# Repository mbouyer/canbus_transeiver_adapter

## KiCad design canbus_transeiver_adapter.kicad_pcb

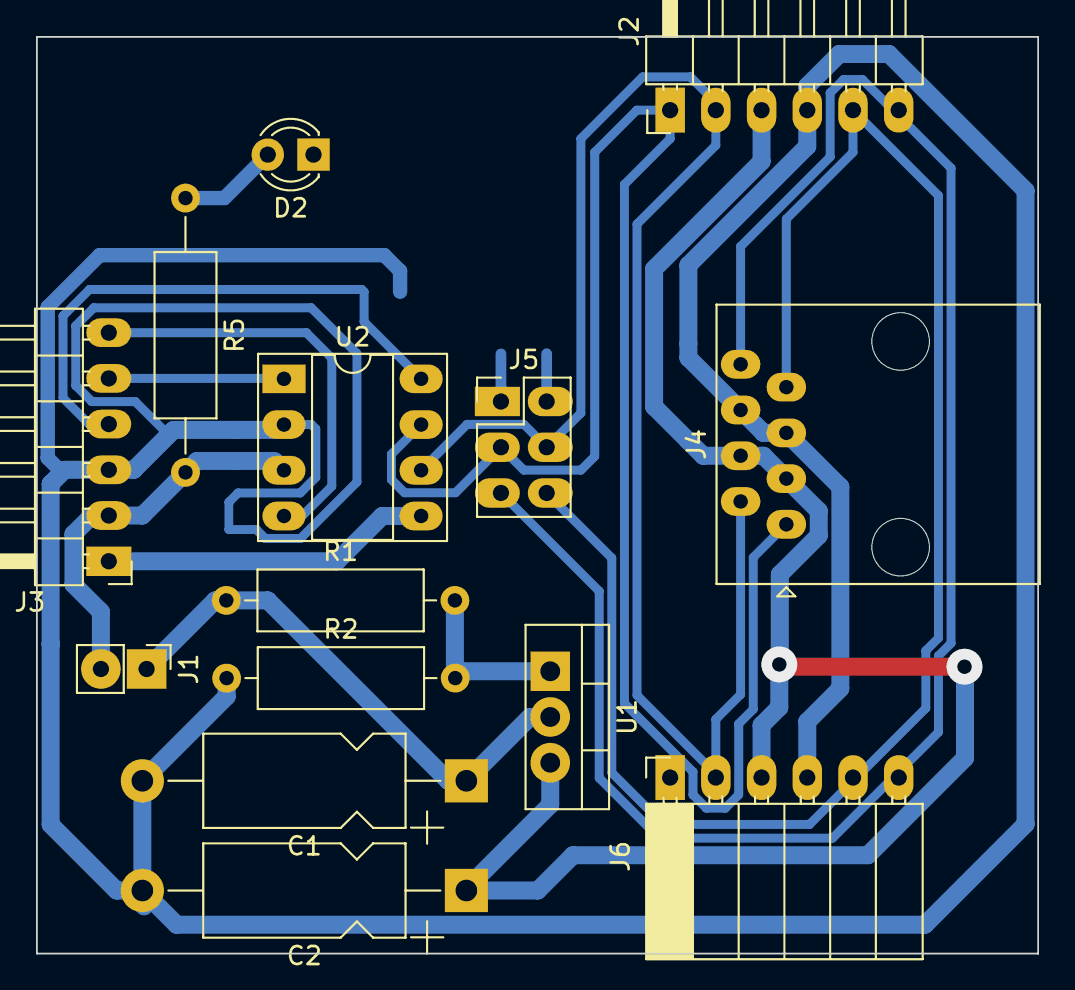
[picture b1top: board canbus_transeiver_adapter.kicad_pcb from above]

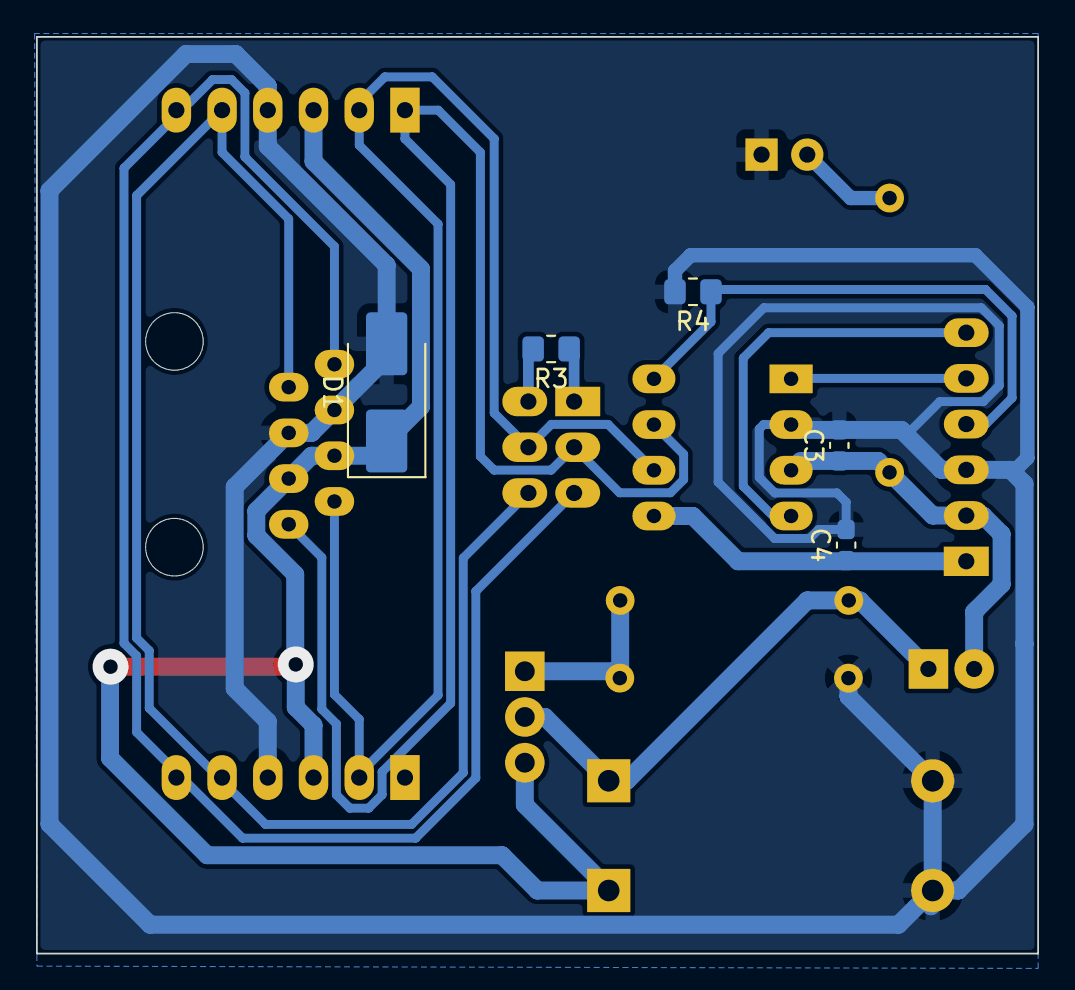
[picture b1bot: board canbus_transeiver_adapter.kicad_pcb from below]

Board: 2 copper layers, 55.6 x 50.9 mm, 19 parts (5 on the bottom side), 16 nets.

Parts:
C1, C2: 10µ; CP_Axial_L11.0mm_D5.0mm_P18.00mm_Horizontal
C3, C4: 100nF; C_0603_1608Metric_Pad1.08x0.95mm_HandSolder
D1: SMBJ16A; D_SMB_Handsoldering
D2: LED; LED_D3.0mm
J1: Conn_01x02_Pin; PinHeader_1x02_P2.54mm_Vertical
J2, J3: Conn_01x06_Pin; PinHeader_1x06_P2.54mm_Horizontal
J4: RJ45; RJ45_Amphenol_54602-x08_Horizontal_handsolder
J5: Conn_02x03_Odd_Even; PinHeader_2x03_P2.54mm_Vertical
J6: Conn_01x06_Socket; PinSocket_1x06_P2.54mm_Horizontal
R1: 120; R_Axial_DIN0309_L9.0mm_D3.2mm_P12.70mm_Horizontal
R2: 360; R_Axial_DIN0309_L9.0mm_D3.2mm_P12.70mm_Horizontal
R3: 100; R_0805_2012Metric_Pad1.20x1.40mm_HandSolder
R4: 10k; R_0805_2012Metric_Pad1.20x1.40mm_HandSolder
R5: 330; R_Axial_DIN0309_L9.0mm_D3.2mm_P15.24mm_Horizontal
U1: LD1117V; TO-220-3_Vertical
U2: MCP2542I/SO; DIP-8_W7.62mm_Socket_LongPads

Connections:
+5V: C3.1, J1.2, J3.2, R5.2, U2.3 (VDD)
/+5VCAN: C1.1, J1.1, R1.1, U1.2 (VO)
/+12CAN: C2.1, D1.1 (A1), J2.3, J4.3, J4.4, J6.3, U1.3 (VI)
/CANH: J2.1, J4.1, J5.3, J6.1, U2.7 (CANH)
/CANL: J2.2, J4.2, J5.4, J6.2, U2.6 (CANL)
/RXD: J3.6, U2.4 (RXD)
/STBY: J3.4, R4.1, U2.8 (STBY)
/TXD: J3.5, U2.1 (TXD)
/VIO: C4.1, J3.1, U2.5 (VIO)
GND: C1.2, C2.2, C3.2, C4.2, D1.2 (A2), D2.1 (K), J2.4, J3.3, J4.5, J4.6, J6.4, R2.1, R4.2, U2.2 (VSS)
unnamed: D2.2 (A), R5.1
unnamed: J2.5, J4.7, J5.6, J6.5
unnamed: J2.6, J4.8, J5.5, J6.6
unnamed: J5.1, R3.1
unnamed: J5.2, R3.2
unnamed: R1.2, R2.2, U1.1 (ADJ)

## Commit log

2023-09-14 First version
2023-11-16 Resize a bit
2023-11-23 Add gerber files
2024-09-24 Add a LED on +5V
